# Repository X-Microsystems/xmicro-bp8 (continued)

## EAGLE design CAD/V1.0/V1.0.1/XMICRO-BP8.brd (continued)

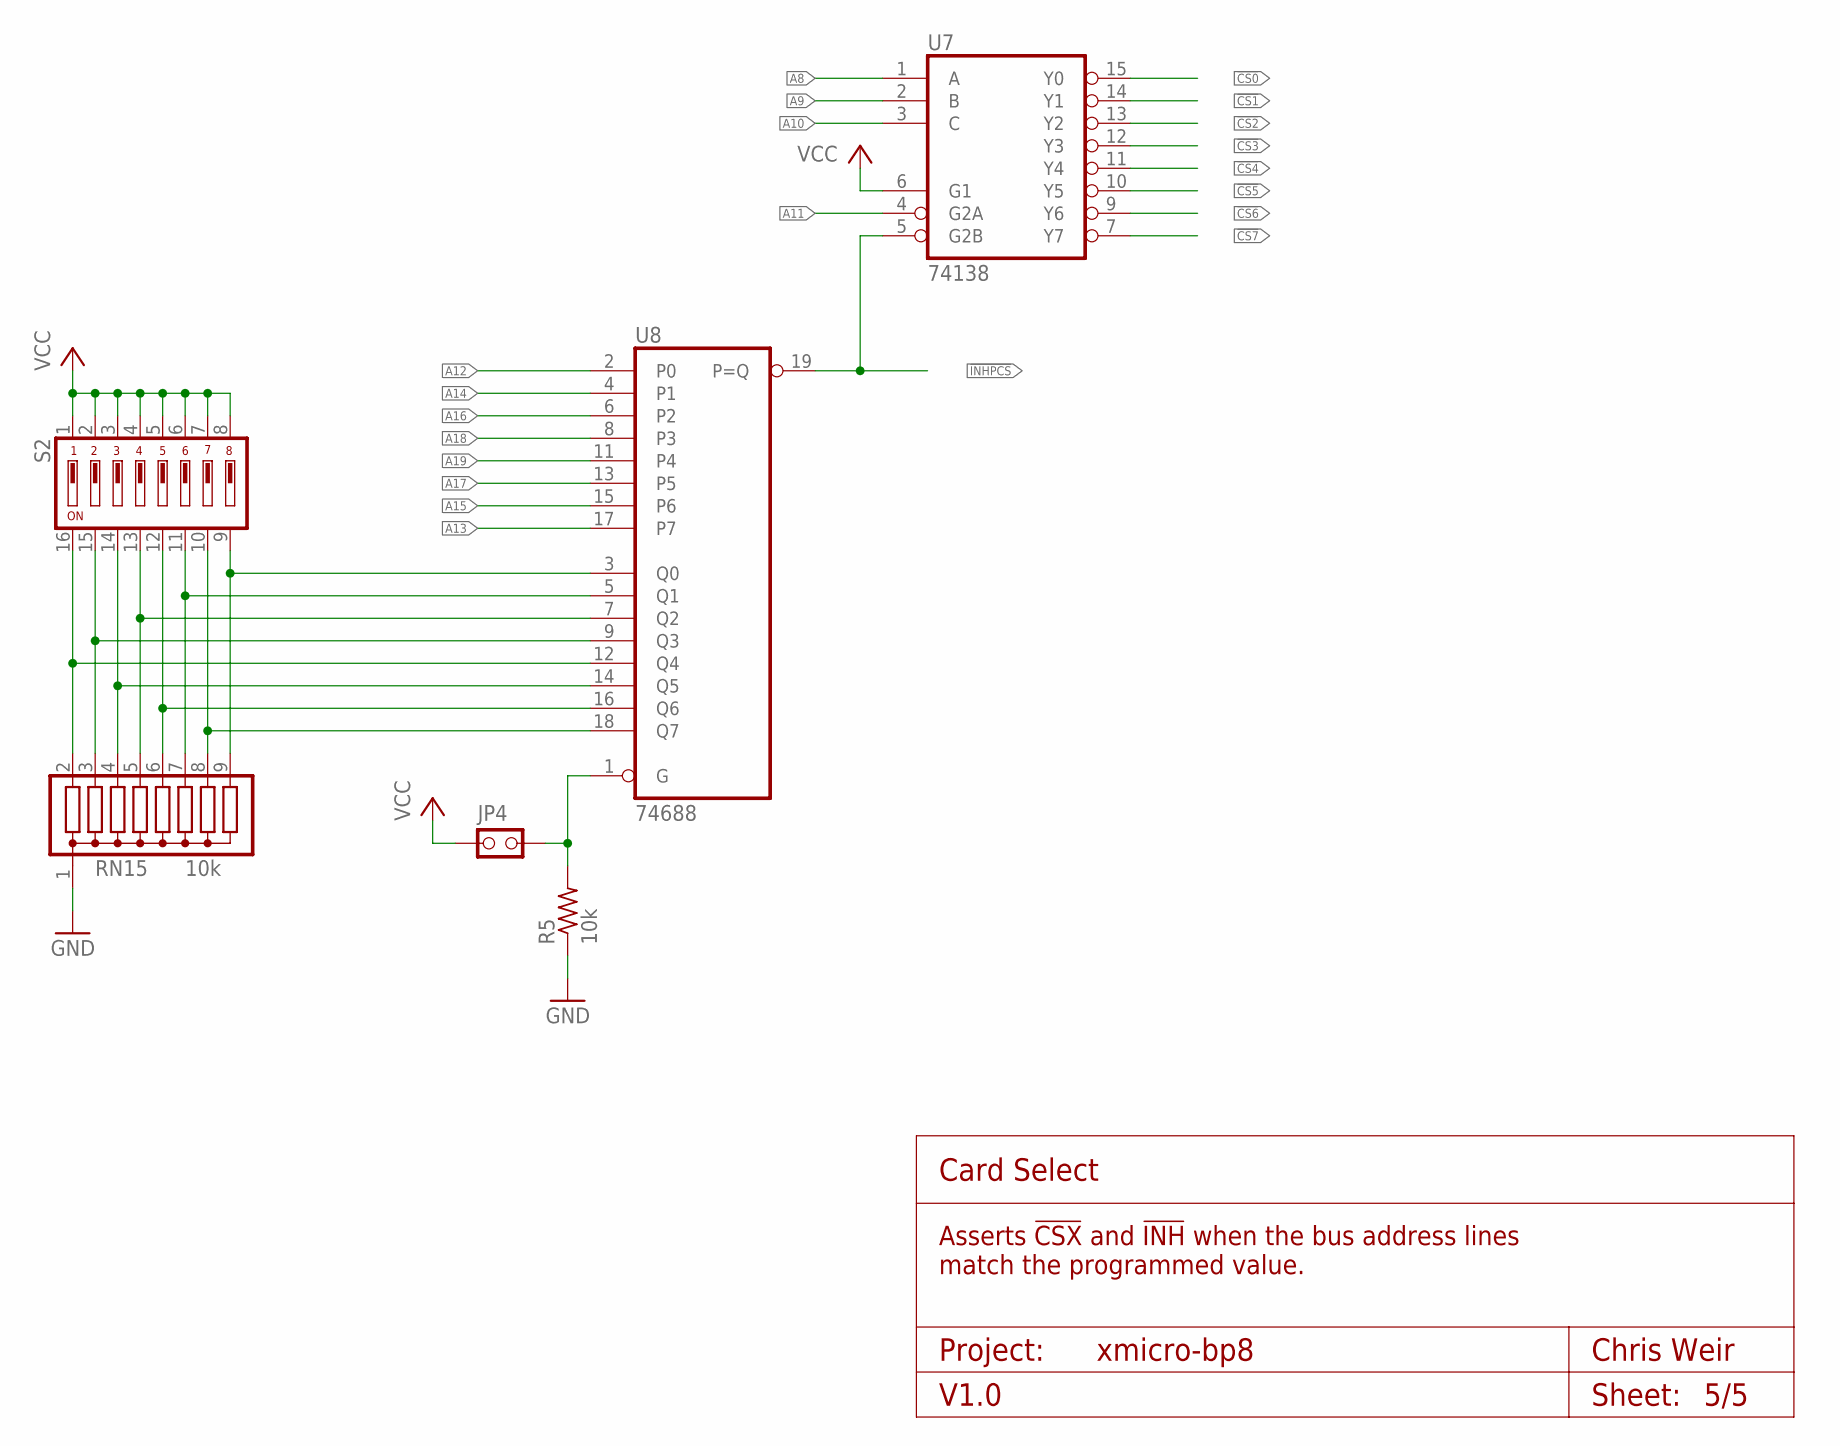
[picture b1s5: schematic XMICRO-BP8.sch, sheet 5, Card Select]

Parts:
JP4: PINHD-1X2THRU; 1X02
R5: 10k; 0207/10
RN15: 10k; SIL9
S2: SW-DIP08; SW-DIP8
U7: 74138; DIL16
U8: 74688; DIL20

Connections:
!CS0: U7.15 (Y0); also elsewhere on the board
!CS1: U7.14 (Y1); also elsewhere on the board
!CS2: U7.13 (Y2); also elsewhere on the board
!CS3: U7.12 (Y3); also elsewhere on the board
!CS4: U7.11 (Y4); also elsewhere on the board
!CS5: U7.10 (Y5); also elsewhere on the board
!CS6: U7.9 (Y6); also elsewhere on the board
!CS7: U7.7 (Y7); also elsewhere on the board
!INHPCS: U7.5 (G2B), U8.19 (P=Q); also elsewhere on the board
A8: U7.1 (A); also elsewhere on the board
A9: U7.2 (B); also elsewhere on the board
A10: U7.3 (C); also elsewhere on the board
A11: U7.4 (G2A); also elsewhere on the board
A12: U8.2 (P0); also elsewhere on the board
A13: U8.17 (P7); also elsewhere on the board
A14: U8.4 (P1); also elsewhere on the board
A15: U8.15 (P6); also elsewhere on the board
A16: U8.6 (P2); also elsewhere on the board
A17: U8.13 (P5); also elsewhere on the board
A18: U8.8 (P3); also elsewhere on the board
A19: U8.11 (P4); also elsewhere on the board
unnamed: RN15.2, S2.16, U8.12 (Q4)
unnamed: RN15.3, S2.15, U8.9 (Q3)
unnamed: RN15.4, S2.14, U8.14 (Q5)
unnamed: RN15.5, S2.13, U8.7 (Q2)
unnamed: RN15.6, S2.12, U8.16 (Q6)
unnamed: RN15.7, S2.11, U8.5 (Q1)
unnamed: RN15.8, S2.10, U8.18 (Q7)
unnamed: RN15.9, S2.9, U8.3 (Q0)
unnamed: JP4.2, R5.2, U8.1 (G)
VCC: JP4.1, S2.1, S2.2, S2.3, S2.4, S2.5, S2.6, S2.7, S2.8, U7.6 (G1), U7.16 (VCC), U8.20 (VCC); also elsewhere on the board

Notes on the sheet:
Card Select
Asserts !CSX! and !INH! when the bus address lines match the programmed value.
Project:
V1.0
Chris Weir
Sheet:

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
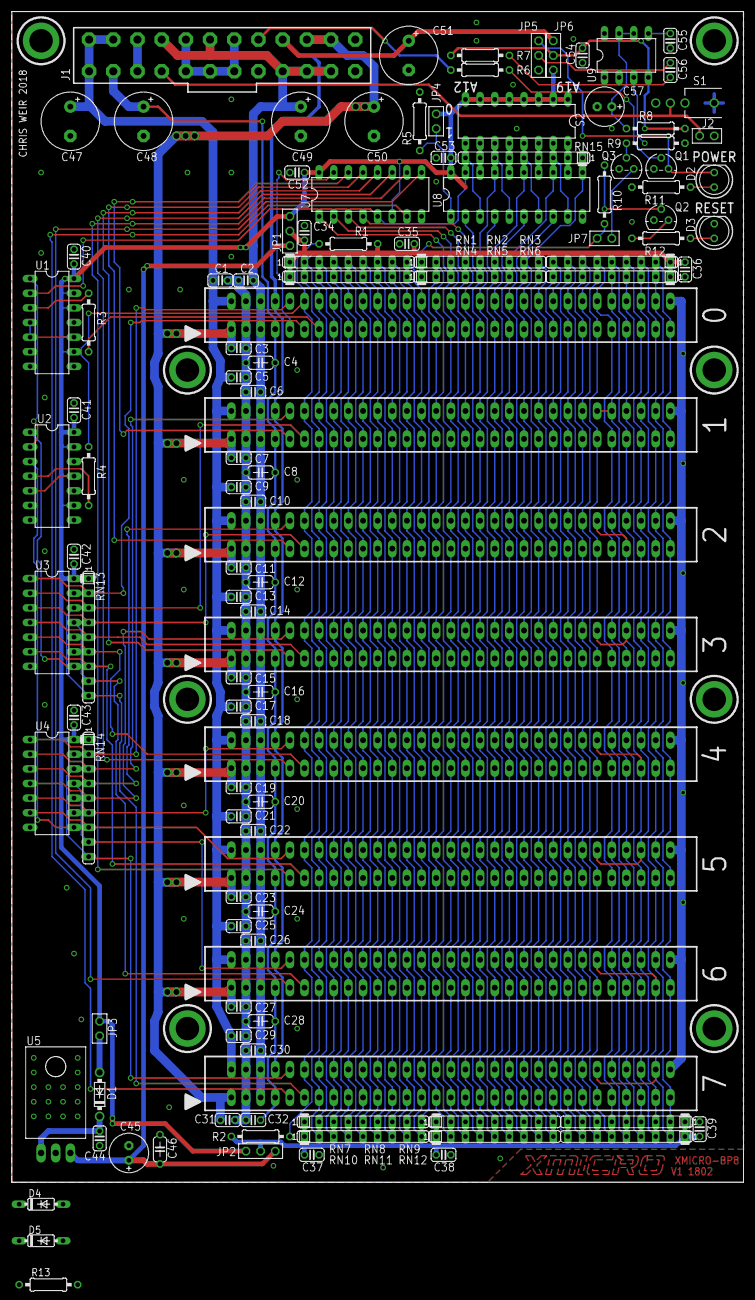
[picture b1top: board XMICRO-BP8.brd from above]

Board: 2 copper layers, 127.0 x 203.2 mm, 119 parts (0 on the bottom side), 116 nets.

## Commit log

2018-08-16 Updated the name in the license
2019-05-28 Updated schematic xrefs to indicate signal direction.
2020-08-30 Added picture and updated README.md
2024-09-15 Updated to Gen 2 V1.0
2024-09-15 Rearranged document files
2024-09-29 Updated datasheet formatting
2024-09-30 Updated datasheet template
2024-10-01 Reduced per-contact current rating from 3.0A (connector spec) to 2.0A (XMICRO bus spec)
2025-08-05 Fixed spelling
2025-08-05 Updated Readme and photos
